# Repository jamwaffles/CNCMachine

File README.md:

# CNCMachine

LinuxCNC config and scripts for my DIY CNC machine

## NFS

<https://askubuntu.com/questions/7117/which-to-use-nfs-or-samba>

Better than Samba. `sudo apt install nfs-common`

In `/etc/fstab`:

```
192.168.0.9:/media/gangstacode  /home/james/GCode  nfs auto,_netdev,rw,hard,intr 0 0
```

## Mount samba share

```bash
mkdir ~/GCode
# yolo
chmod 0777 ~/GCode 
sudo apt install gvfs-backends samba cifs-utils
```

Then in `/etc/fstab`:

```
//octahedron.house/gangstacode /home/james/GCode cifs username=james,password=[password],iocharset=utf8,file_mode=0777,dir_mode=0777,noperm 0 0
```

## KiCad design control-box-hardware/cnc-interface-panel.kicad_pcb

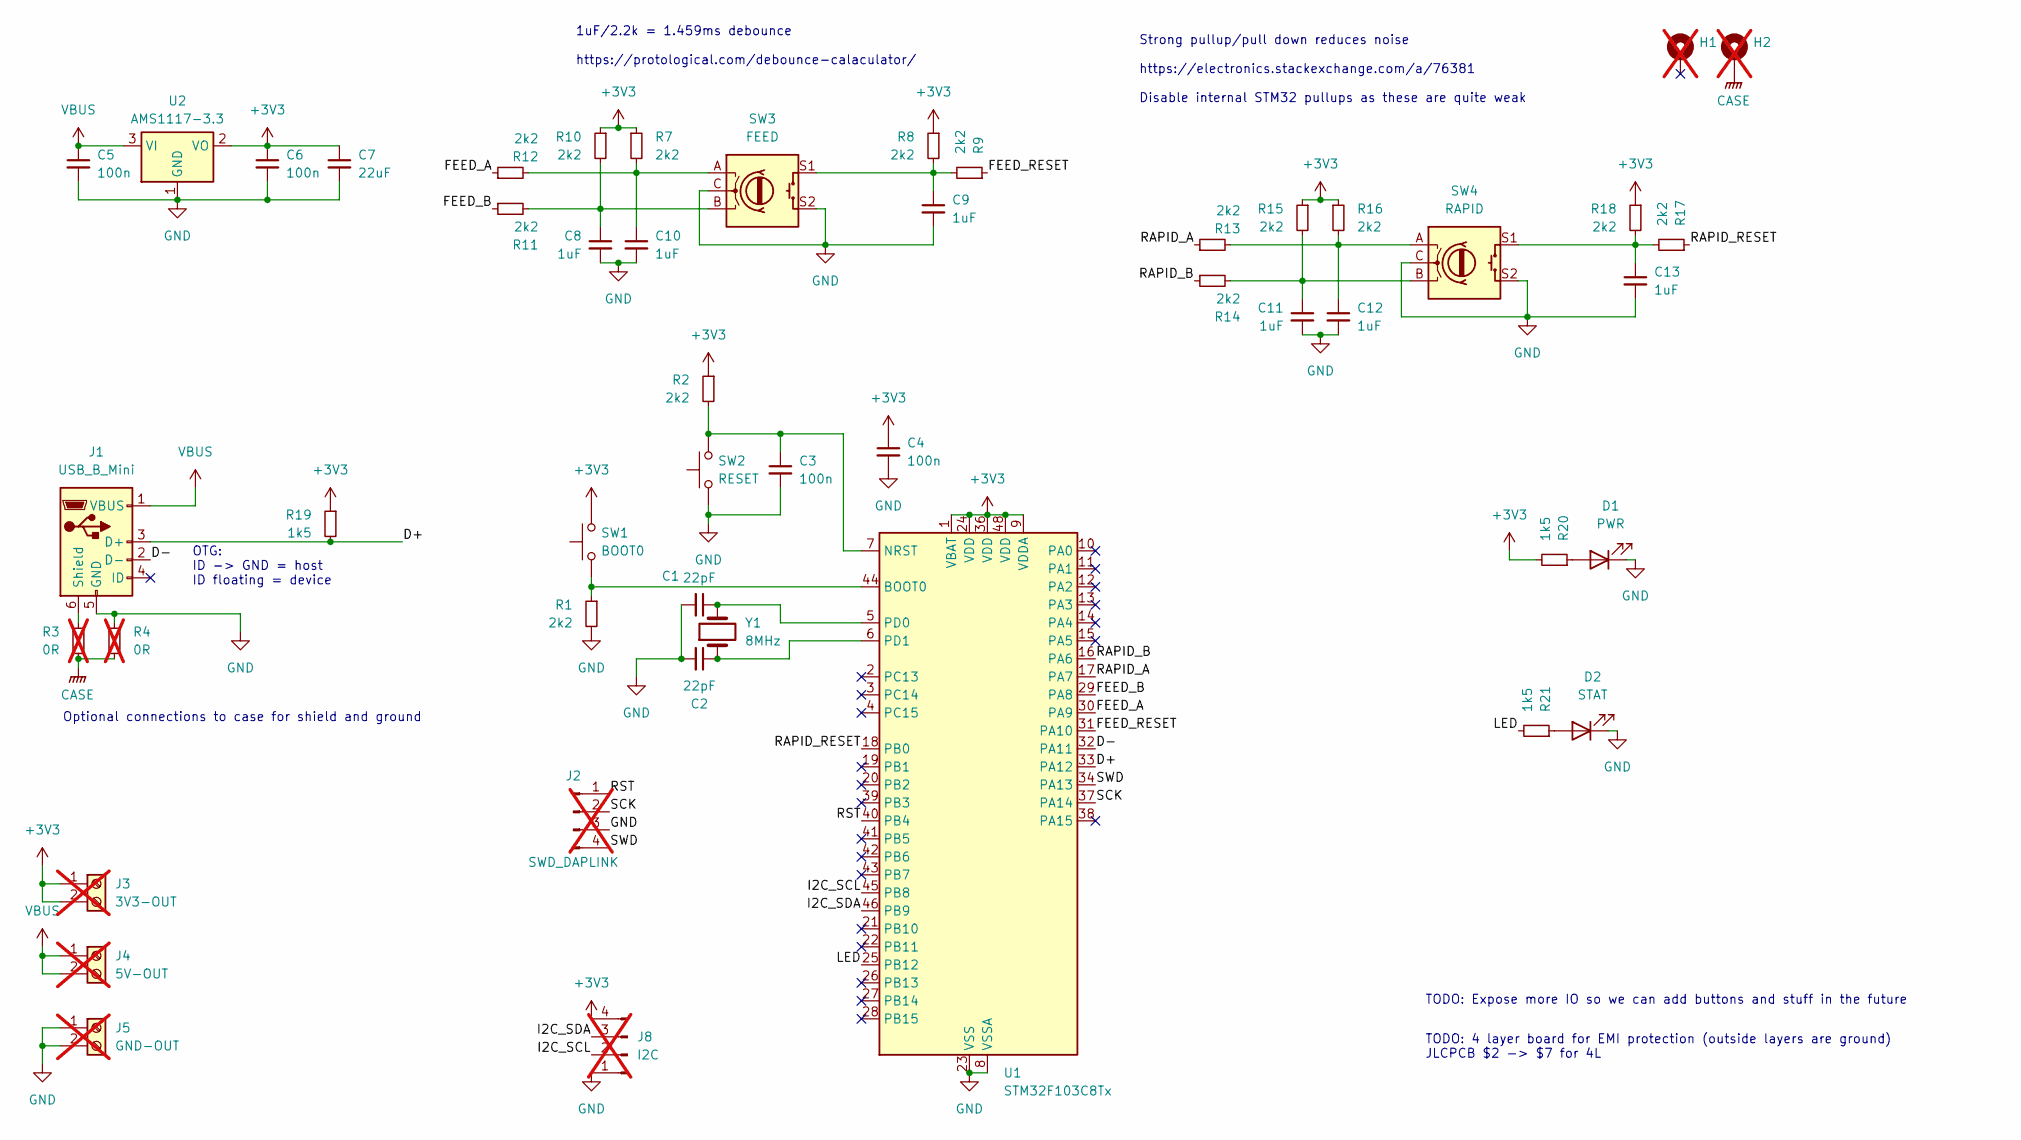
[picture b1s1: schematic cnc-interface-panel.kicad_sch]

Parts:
C1, C2: 22pF; C_0603_1608Metric_Pad1.08x0.95mm_HandSolder; MPN CL10C220JB8NNNC; JLCPCB C1653
C3, C4, C5, C6: 100n; C_0603_1608Metric_Pad1.08x0.95mm_HandSolder; MPN CC0603KRX7R9BB104; JLCPCB C14663
C7: 22uF; C_0603_1608Metric_Pad1.08x0.95mm_HandSolder; MPN CL10A226MQ8NRNC; JLCPCB C59461
C8, C9, C10, C11, C12, C13: 1uF; C_0603_1608Metric_Pad1.08x0.95mm_HandSolder; MPN CL10A105KB8NNNC; JLCPCB C15849
D1: PWR; LED_0603_1608Metric; MPN KT-0603W; JLCPCB C2290
D2: STAT; LED_0603_1608Metric; MPN KT-0603W; JLCPCB C2290
H1, H2: MountingHole_3.2mm_M3_Pad_Via; not fitted
J1: USB_B_Mini; molex-usb-mini-b-67503-1020; MPN 67503-1020; JLCPCB C136451
J2: SWD_DAPLINK; PinHeader_1x04_P2.54mm_Vertical; not fitted
J3: 3V3-OUT; TerminalBlock_Phoenix_MKDS-1,5-2_1x02_P5.00mm_Horizontal; not fitted
J4: 5V-OUT; TerminalBlock_Phoenix_MKDS-1,5-2_1x02_P5.00mm_Horizontal; not fitted
J5: GND-OUT; TerminalBlock_Phoenix_MKDS-1,5-2_1x02_P5.00mm_Horizontal; not fitted
J8: I2C; PinHeader_1x04_P2.54mm_Vertical; not fitted
R1, R2, R7, R8, R9, R10, R11, R12, R13, R14, R15, R16, R17, R18: 2k2; R_0603_1608Metric_Pad0.98x0.95mm_HandSolder; MPN 0603WAF2201T5E; JLCPCB C4190
R3, R4: 0R; R_0603_1608Metric_Pad0.98x0.95mm_HandSolder; MPN 0603WAF0000T5E; JLCPCB C21189; not fitted
R19, R20, R21: 1k5; R_0603_1608Metric_Pad0.98x0.95mm_HandSolder; MPN 0603WAF1501T5E; JLCPCB C22843
SW1: BOOT0; TS-1187A-B-A-B; MPN TS-1187A-B-A-B; JLCPCB C318884
SW2: RESET; TS-1187A-B-A-B; MPN TS-1187A-B-A-B; JLCPCB C318884
SW3: FEED; PEC11L4115FS0020; MPN PEC11L-4115F-S0020; JLCPCB C143799
SW4: RAPID; PEC11L4115FS0020; MPN PEC11L-4115F-S0020; JLCPCB C143799
U1: STM32F103C8Tx; LQFP-48_7x7mm_P0.5mm; MPN STM32F103C8T6; JLCPCB C8734
U2: AMS1117-3.3; SOT-223-3_TabPin2; MPN AMS1117-3.3; JLCPCB C6186
Y1: 8MHz; Crystal_SMD_TXC_7A-2Pin_5x3.2mm; MPN X50328MSB2GI; JLCPCB C115962

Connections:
+3V3: C4.1, C6.1, C7.1, J3.1, J3.2, J8.4, R2.1, R7.1, R8.1, R10.1, R15.1, R16.1, R18.1, R19.1, R20.2, SW1.2, U1.1 (VBAT), U1.9 (VDDA), U1.24 (VDD), U1.36 (VDD), U1.48 (VDD), U2.2 (VO)
/D+: J1.3 (D+), R19.2, U1.33 (PA12)
/D-: J1.2 (D-), U1.32 (PA11)
/FEED_A: R12.1, U1.30 (PA9)
/FEED_B: R11.1, U1.29 (PA8)
/FEED_RESET: R9.1, U1.31 (PA10)
/I2C_SCL: J8.2, U1.45 (PB8)
/I2C_SDA: J8.3, U1.46 (PB9)
/LED: R21.2, U1.25 (PB12)
/RAPID_A: R13.1, U1.17 (PA7)
/RAPID_B: R14.1, U1.16 (PA6)
/RAPID_RESET: R17.1, U1.18 (PB0)
/RST: J2.1, U1.40 (PB4)
/SCK: J2.2, U1.37 (PA14)
/SWD: J2.4, U1.34 (PA13)
CASE: H2.1, R3.2, R4.2
GND: C1.2, C2.2, C3.2, C4.2, C5.2, C6.2, C7.2, C8.2, C9.2, C10.2, C11.2, C12.2, C13.2, D1.1 (K), D2.1 (K), J1.5 (GND), J2.3, J5.1, J5.2, J8.1, R1.2, R4.1, SW2.1, SW3.C, SW3.S2, SW4.C, SW4.S2, U1.8 (VSSA), U1.23 (VSS), U1.35 (VSS), U1.47 (VSS), U2.1 (GND)
unnamed: C8.1, R10.2, R11.2, SW3.B
unnamed: C9.1, R8.2, R9.2, SW3.S1
unnamed: C10.1, R7.2, R12.2, SW3.A
unnamed: C11.1, R14.2, R15.2, SW4.B
unnamed: C12.1, R13.2, R16.2, SW4.A
unnamed: C13.1, R17.2, R18.2, SW4.S1
unnamed: D1.2 (A), R20.1
unnamed: D2.2 (A), R21.1
unnamed: J1.6 (Shield), R3.1
unnamed: R1.1, SW1.1, U1.44 (BOOT0)
unnamed: C3.1, R2.2, SW2.2, U1.7 (NRST)
unnamed: C1.1, U1.5 (PD0), Y1.2
unnamed: C2.1, U1.6 (PD1), Y1.1
VBUS: C5.1, J1.1 (VBUS), J4.1, J4.2, U2.3 (VI)

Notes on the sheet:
OTG: ID -> GND = host ID floating = device
Strong pullup/pull down reduces noise https://electronics.stackexchange.com/a/76381 Disable internal STM32 pullups as these are quite weak
Optional connections to case for shield and ground
TODO: 4 layer board for EMI protection (outside layers are ground) JLCPCB $2 -> $7 for 4L
1uF/2.2k = 1.459ms debounce https://protological.com/debounce-calaculator/
TODO: Expose more IO so we can add buttons and stuff in the future

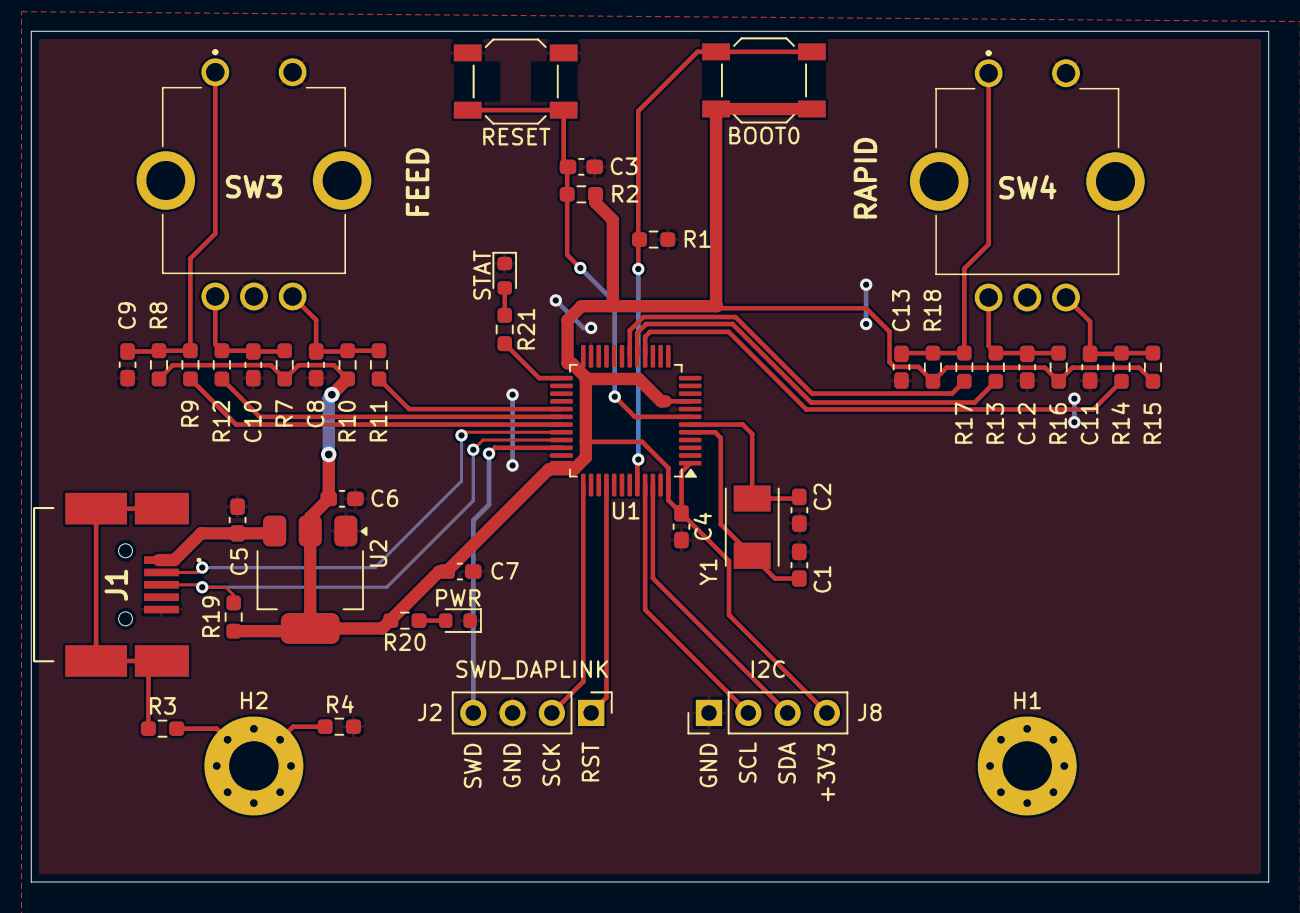
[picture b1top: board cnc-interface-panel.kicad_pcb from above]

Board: 2 copper layers, 80.0 x 55.0 mm, 46 parts (0 on the bottom side), 31 nets.

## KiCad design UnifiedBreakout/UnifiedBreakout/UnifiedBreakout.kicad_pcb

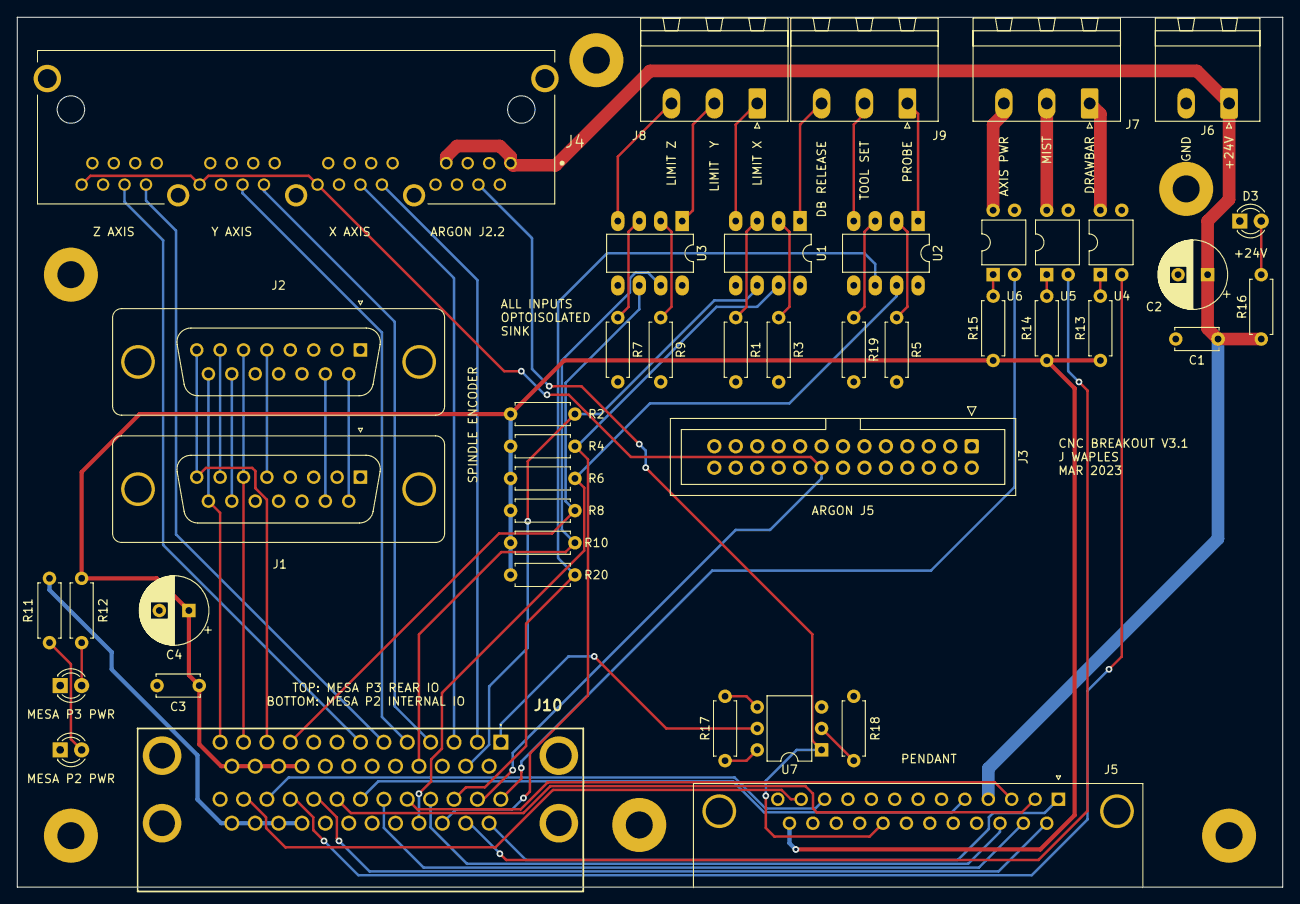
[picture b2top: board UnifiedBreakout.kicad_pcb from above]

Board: 2 copper layers, 149.9 x 103.0 mm, 50 parts (0 on the bottom side), 61 nets.

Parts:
C1, C3: 100n; C_Disc_D5.0mm_W2.5mm_P5.00mm
C2, C4: 100uF; CP_Radial_D8.0mm_P3.50mm
D1: MESA P3 PWR; LED_D3.0mm
D2: MESA P2 PWR; LED_D3.0mm
D3: +24V; LED_D3.0mm
H1, H2, H3, H4, H5, H6: MountingHole; MountingHole_3.2mm_M3_Pad
J1, J2: DA15_Receptacle_MountingHoles; DSUB-15_Female_Vertical_P2.77x2.84mm_MountingHoles
J3: ARGON J5; IDC-Header_2x13_P2.54mm_Vertical
J4: SS71800-041F
J5: PENDANT; DSUB-25_Female_Horizontal_P2.77x2.84mm_EdgePinOffset7.70mm_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
J6: 24V BUS; PhoenixContact_MSTBA_2,5_2-G-5,08_1x02_P5.08mm_Horizontal
J7: DRAWBAR+MIST+AXIS_PWR; PhoenixContact_MSTBA_2,5_3-G-5,08_1x03_P5.08mm_Horizontal
J8: LIMIT; PhoenixContact_MSTBA_2,5_3-G-5,08_1x03_P5.08mm_Horizontal
J9: AUX; PhoenixContact_MSTBA_2,5_3-G-5,08_1x03_P5.08mm_Horizontal
J10: DB25_Receptacle_Dual; NorComp-Dual-DB25
R1, R3, R5, R7, R9, R16, R18, R19: 2K2; R_Axial_DIN0207_L6.3mm_D2.5mm_P7.62mm_Horizontal
R2, R4, R6, R8, R10, R20: 10K; R_Axial_DIN0207_L6.3mm_D2.5mm_P7.62mm_Horizontal
R11, R12: 220R; R_Axial_DIN0207_L6.3mm_D2.5mm_P7.62mm_Horizontal
R13, R14, R15: 680R; R_Axial_DIN0207_L6.3mm_D2.5mm_P7.62mm_Horizontal
R17: 220K; R_Axial_DIN0207_L6.3mm_D2.5mm_P7.62mm_Horizontal
U1, U2, U3: ILD74; DIP-8_W7.62mm_LongPads
U4, U5, U6: G3VM-61A1; DIP-4_W7.62mm
U7: 4N35; DIP-6_W7.62mm

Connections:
+5VP: C3.1, C4.1, J5.25, J10.A22, J10.A23, J10.A24, J10.A25, R2.1, R4.1, R6.1, R8.1, R10.1, R11.2, R13.1, R14.1, R15.1, R20.1
+24V: C1.1, C2.1, J4.1_1, J4.7_1, J5.4, J6.1, R16.2
/ALARM: J3.16, J4.8_2, J4.8_3, J4.8_4, J10.B2
/ARGON ENCODER/A-: J1.7, J2.7
/ARGON ENCODER/B-: J1.5, J2.5
/ARGON ENCODER/IDX-: J1.14, J2.14
/ARGON ESTOP/ESTOP+: J4.4_1, J5.21, U7.1
/AXIS_PWR: J10.B1, U6.2
/DRAWBAR SW/INPUT: J9.3, U1.1
/DRAWBAR_SW: J10.B16, R4.2, U1.7
/DRAWBAR_VALVE: J10.B10, U4.2
/ESTOP: J10.A1, U7.5
/LIM X/INPUT: J8.1, U1.4
/LIM Y/INPUT: J8.2, U3.1
/LIM Z/INPUT: J8.3, U3.4
/LIMIT_X: J10.A15, R2.2, U1.6
/LIMIT_Y: J10.A17, R10.2, U3.7
/LIMIT_Z: J10.A10, R8.2, U3.6
/MESA P2 INTERNAL IO/MESA_5V: J10.B22, J10.B23, J10.B24, J10.B25, R12.1
/MESA P3 REAR IO/IO_02_STEPGEN_00_STEP: J4.2_2, J10.A2
/MESA P3 REAR IO/IO_04_STEPGEN_00_DIR: J4.4_2, J10.A3
/MESA P3 REAR IO/IO_06_STEPGEN_01_STEP: J4.2_3, J10.A4
/MESA P3 REAR IO/IO_08_STEPGEN_01_DIR: J4.4_3, J10.A5
/MESA P3 REAR IO/IO_09_STEPGEN_02_STEP: J4.2_4, J10.A6
/MESA P3 REAR IO/IO_10_STEPGEN_02_DIR: J4.4_4, J10.A7
/MESA_P3_5V: D2.2 (A), R12.2
/MIST: J10.B15, U5.2
/PENDANT_ENC_A: J5.11, J10.B11
/PENDANT_ENC_B: J5.12, J10.B12
/PENDANT_MULX1: J5.15, J10.B6
/PENDANT_MULX10: J5.3, J10.B5
/PENDANT_MULX100: J5.16, J10.B4
/PENDANT_SELA: J5.5, J10.B7
/PENDANT_SELX: J5.1, J10.B14
/PENDANT_SELY: J5.14, J10.B9
/PENDANT_SELZ: J5.2, J10.B8
/PROBE: J10.B17, R6.2, U2.7
/PROBE/INPUT: J9.1, U2.1
/SPINDLE_ENC_A: J1.8, J2.8, J10.A11
/SPINDLE_ENC_B: J1.6, J2.6, J10.A12
/SPINDLE_ENC_IDX: J1.15, J2.15, J10.A13
/TOOL_PROBE: J10.B3, R20.2, U2.6
/TOOL_PROBE/INPUT: J9.2, U2.4
GND: C1.2, C2.2, C3.2, C4.2, D1.1 (K), D2.1 (K), D3.1 (K), J1.0 (PAD), J1.10, J2.0 (PAD), J2.10, J3.1, J3.15, J4.1_2, J4.1_3, J4.1_4, J4.3_2, J4.3_3, J4.3_4, J4.5_1, J4.5_2, J4.5_3, J4.5_4, J4.7_2, J4.7_3, J4.7_4, J4.8_1, J5.0 (PAD), J5.19, J5.20, J6.2, J10.A18, J10.A19, J10.A20, J10.A21, J10.B18, J10.B19, J10.B20, J10.B21, J10.MH1, J10.MH2, J10.MH3, J10.MH4, R1.2, R3.2, R5.2, R7.2, R9.2, R17.2, R18.2, R19.2, U1.5, U1.8, U2.5, U2.8, U3.5, U3.8, U4.3, U5.3, U6.3, U7.4
unnamed: D1.2 (A), R11.1
unnamed: D3.2 (A), R16.1
unnamed: J1.9, J2.9
unnamed: J7.1, U4.4
unnamed: J7.2, U5.4
unnamed: J7.3, U6.4
unnamed: R1.1, U1.3
unnamed: R3.1, U1.2
unnamed: R5.1, U2.2
unnamed: R7.1, U3.3
unnamed: R9.1, U3.2
unnamed: R13.2, U4.1
unnamed: R14.2, U5.1
unnamed: R15.2, U6.1
unnamed: R17.1, U7.6
unnamed: R18.1, U7.2
unnamed: R19.1, U2.3

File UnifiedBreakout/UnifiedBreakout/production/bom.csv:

Designator,Footprint,Quantity,Value,LCSC Part #
"C1, C3",C_Disc_D5.0mm_W2.5mm_P5.00mm,2,100n,K104K15X7RF53H5
"C2, C4",CP_Radial_D8.0mm_P3.50mm,2,100uF,35RX30100M8X11.5 
D1,LED_D3.0mm,1,MESA P3 PWR,MCL034GD 
D2,LED_D3.0mm,1,MESA P2 PWR,MCL034GD 
D3,LED_D3.0mm,1,+24V,MCL034MT
"H1, H2, H3, H4, H5, H6",MountingHole_3.2mm_M3_Pad,6,MountingHole,
"J1, J2",DSUB-15_Female_Vertical_P2.77x2.84mm_MountingHoles,2,DA15_Receptacle_MountingHoles,D15S24A4GV00LF 
J10,NorComp-Dual-DB25,1,DB25_Receptacle_Dual,178-025-513R571
J3,IDC-Header_2x13_P2.54mm_Vertical,1,ARGON J5,61202621621
J4,SS71800-041F,1,~,SS71800-041F
J5,DSUB-25_Female_Horizontal_P2.77x2.84mm_EdgePinOffset7.70mm_Housed_MountingHolesOffset9.12mm,1,PENDANT,5747846-4 
J6,"PhoenixContact_MSTBA_2,5_2-G-5,08_1x02_P5.08mm_Horizontal",1,24V BUS,1757242
J7,"PhoenixContact_MSTBA_2,5_3-G-5,08_1x03_P5.08mm_Horizontal",1,DRAWBAR+MIST+AXIS_PWR,1757255
J8,"PhoenixContact_MSTBA_2,5_3-G-5,08_1x03_P5.08mm_Horizontal",1,LIMIT,1757255
J9,"PhoenixContact_MSTBA_2,5_3-G-5,08_1x03_P5.08mm_Horizontal",1,AUX,1757255
"R1, R16, R18, R19, R3, R5, R7, R9",R_Axial_DIN0207_L6.3mm_D2.5mm_P7.62mm_Horizontal,8,2K2,MF25 2K2
"R10, R2, R20, R4, R6, R8",R_Axial_DIN0207_L6.3mm_D2.5mm_P7.62mm_Horizontal,6,10K,MF25 10K
"R11, R12",R_Axial_DIN0207_L6.3mm_D2.5mm_P7.62mm_Horizontal,2,220R,MF25 220R
"R13, R14, R15",R_Axial_DIN0207_L6.3mm_D2.5mm_P7.62mm_Horizontal,3,680R,MF25 680R
R17,R_Axial_DIN0207_L6.3mm_D2.5mm_P7.62mm_Horizontal,1,220K,MF25 220K
"U1, U2, U3",DIP-8_W7.62mm_LongPads,3,ILD74,ILD74 
"U4, U5, U6",DIP-4_W7.62mm,3,G3VM-61A1 ,G3VM-61A1
U7,DIP-6_W7.62mm,1,4N35,4N35

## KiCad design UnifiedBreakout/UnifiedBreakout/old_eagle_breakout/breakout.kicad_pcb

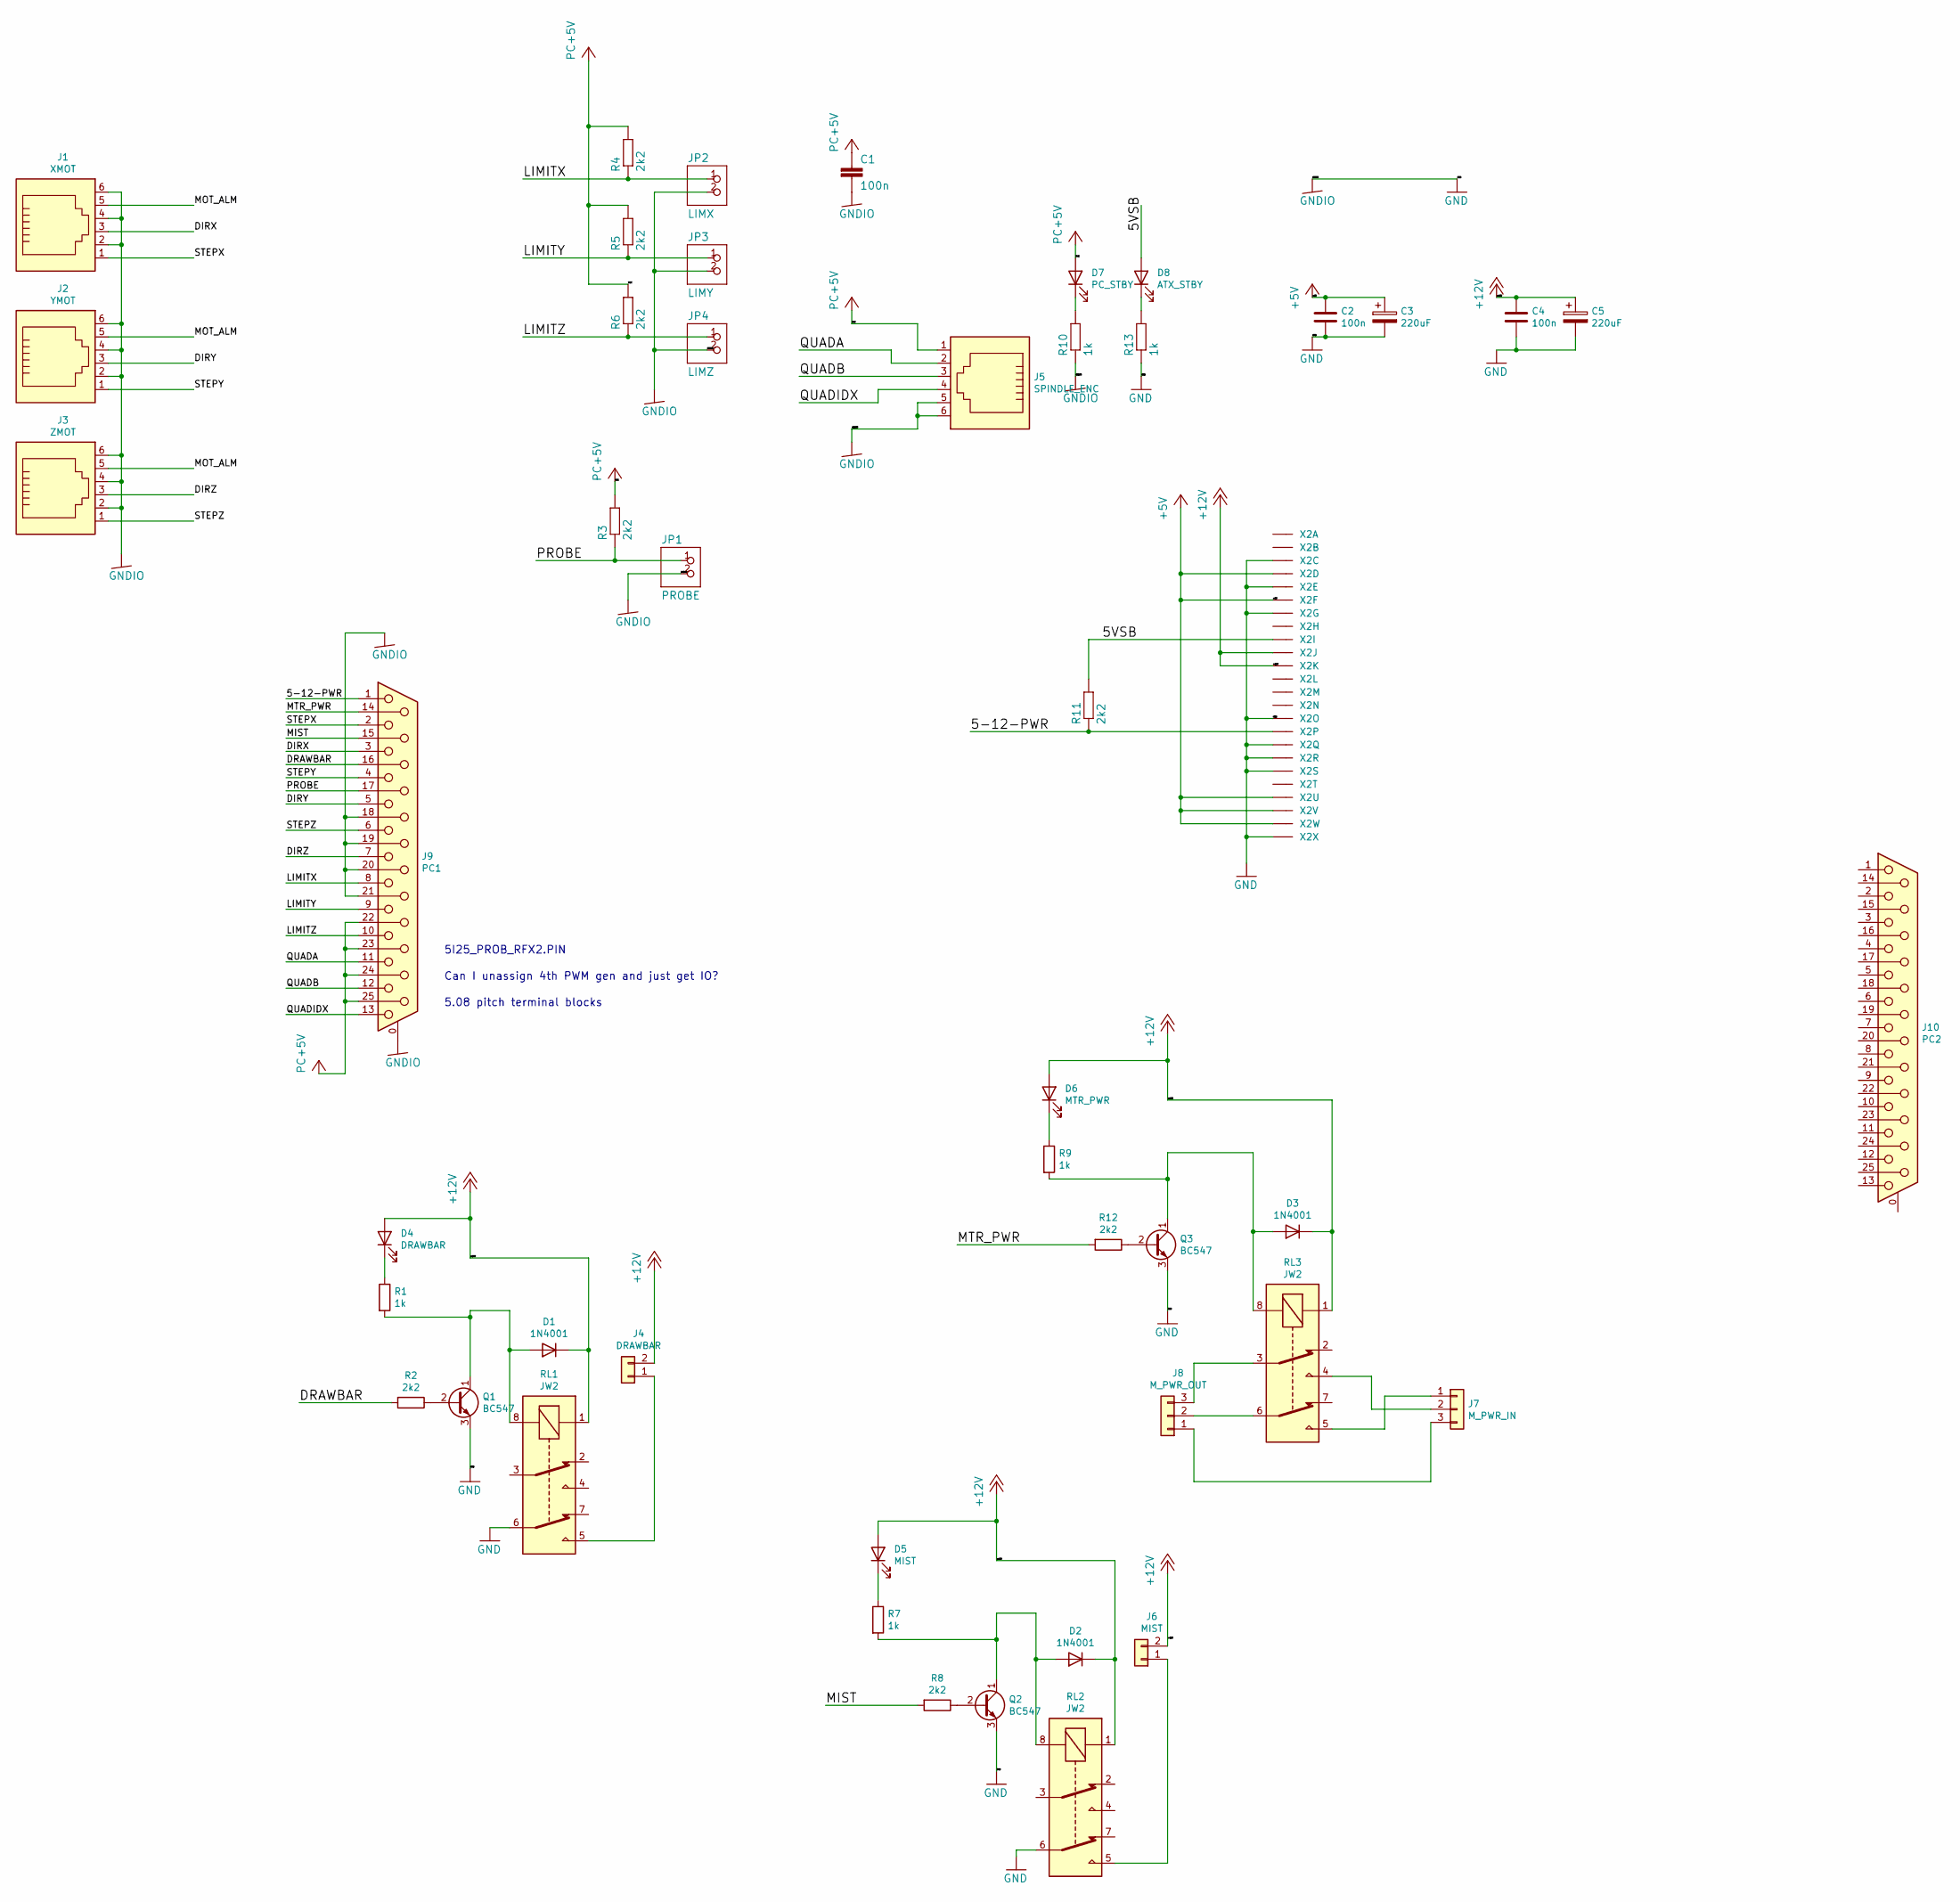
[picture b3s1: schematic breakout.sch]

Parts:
C1: 100n; C_Rect_L7.0mm_W2.5mm_P5.00mm
C2, C4: 100n; C_Disc_D8.0mm_W2.5mm_P5.00mm
C3, C5: 220uF; CP_Radial_D8.0mm_P3.80mm
D1, D2, D3: 1N4001; D_DO-41_SOD81_P10.16mm_Horizontal
D4: DRAWBAR; LED_D3.0mm
D5: MIST; LED_D3.0mm
D6: MTR_PWR; LED_D3.0mm
D7: PC_STBY; LED_D3.0mm
D8: ATX_STBY; LED_D3.0mm
J1: XMOT; 6p6c
J2: YMOT; 6p6c
J3: ZMOT; 6p6c
J4: DRAWBAR; kk156_26-60-4020
J5: SPINDLE_ENC; 6p6c
J6: MIST; kk156_26-60-4020
J7: M_PWR_IN; kk156_26-60-4030
J8: M_PWR_OUT; kk156_26-60-4030
J9: PC1; DB_25F
J10: PC2; DB_25F
JP1: PROBE; rca_yellow
JP2: LIMX; rca_black
JP3: LIMY; rca_black
JP4: LIMZ; rca_black
Q1, Q2, Q3: BC547; TO-92_Inline_Wide
R1, R7, R9, R10, R13: 1k; R_Axial_DIN0207_L6.3mm_D2.5mm_P7.62mm_Horizontal
R2, R3, R4, R5, R6, R8, R11, R12: 2k2; R_Axial_DIN0207_L6.3mm_D2.5mm_P7.62mm_Horizontal
RL1, RL2, RL3: JW2; Relay_DPDT_Panasonic_JW2
X2: 5566-24; Molex_Mini-Fit_Jr_5566-24A_2x12_P4.20mm_Vertical

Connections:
+5V: C2.1, C3.1, X2.4, X2.6, X2.21, X2.22, X2.23
+12V: C4.1, C5.1, D1.1 (K), D2.1 (K), D3.1 (K), D4.2 (A), D5.2 (A), D6.2 (A), J4.2, J6.2, RL1.1, RL2.1, RL3.1, X2.10, X2.11
/5-12-PWR: J9.1, R11.1, X2.16; also elsewhere on the board
/5VSB: D8.2 (A), R11.2, X2.9
/DIRX: J1.3, J9.3; also elsewhere on the board
/DIRY: J2.3, J9.5; also elsewhere on the board
/DIRZ: J3.3, J9.7; also elsewhere on the board
/DRAWBAR: J9.16, R2.2; also elsewhere on the board
/LIMITX: J9.8, JP2.1, R4.1; also elsewhere on the board
/LIMITY: J9.9, JP3.1, R5.1; also elsewhere on the board
/LIMITZ: J9.10, JP4.1, R6.1; also elsewhere on the board
/MIST: J9.15, R8.2; also elsewhere on the board
/MOT_ALM: J1.5, J2.5, J3.5
/MTR_PWR: J9.14, R12.2; also elsewhere on the board
/PROBE: J9.17, JP1.1, R3.1; also elsewhere on the board
/QUADA: J5.2, J9.11; also elsewhere on the board
/QUADB: J5.3, J9.12; also elsewhere on the board
/QUADIDX: J5.4, J9.13; also elsewhere on the board
/STEPX: J1.1, J9.2; also elsewhere on the board
/STEPY: J2.1, J9.4; also elsewhere on the board
/STEPZ: J3.1, J9.6; also elsewhere on the board
GND: C1.2, C2.2, C3.2, C4.2, C5.2, J1.2, J1.4, J1.6, J2.2, J2.4, J2.6, J3.2, J3.4, J3.6, J5.5, J5.6, J9.0 (PAD), J9.18, J9.19, J9.20, J9.21, JP1.2, JP2.2, JP3.2, JP4.2, Q1.3 (E), Q2.3 (E), Q3.3 (E), R10.1, R13.1, RL1.6, RL2.6, X2.3, X2.5, X2.7, X2.15, X2.17, X2.18, X2.19, X2.24; also elsewhere on the board
unnamed: D1.2 (A), Q1.1 (C), R1.2, RL1.8
unnamed: D2.2 (A), Q2.1 (C), R7.2, RL2.8
unnamed: D3.2 (A), Q3.1 (C), R9.2, RL3.8
unnamed: D4.1 (K), R1.1
unnamed: D5.1 (K), R7.1
unnamed: D6.1 (K), R9.1
unnamed: D7.1 (K), R10.2
unnamed: D8.1 (K), R13.2
unnamed: J4.1, RL1.5
unnamed: J6.1, RL2.5
unnamed: J7.1, RL3.5
unnamed: J7.2, RL3.4
unnamed: J7.3, J8.1
unnamed: J8.2, RL3.6
unnamed: J8.3, RL3.3
unnamed: Q1.2 (B), R2.1
unnamed: Q2.2 (B), R8.1
unnamed: Q3.2 (B), R12.1
VCC: C1.1, D7.2 (A), J5.1, J9.22, J9.23, J9.24, J9.25, R3.2, R4.2, R5.2, R6.2; also elsewhere on the board

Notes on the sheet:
5I25_PROB_RFX2.PIN
5.08 pitch terminal blocks
Can I unassign 4th PWM gen and just get IO?

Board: 2 copper layers, 48 parts (0 on the bottom side), 41 nets, no tracks yet.

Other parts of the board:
X1: PC; DB_25F

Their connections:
/5-12-PWR: X1.1; also elsewhere on the board
/DIRX: X1.3; also elsewhere on the board
/DIRY: X1.5; also elsewhere on the board
/DIRZ: X1.7; also elsewhere on the board
/DRAWBAR: X1.16; also elsewhere on the board
/LIMITX: X1.8; also elsewhere on the board
/LIMITY: X1.9; also elsewhere on the board
/LIMITZ: X1.10; also elsewhere on the board
/MIST: X1.15; also elsewhere on the board
/MTR_PWR: X1.14; also elsewhere on the board
/PROBE: X1.17; also elsewhere on the board
/QUADA: X1.11; also elsewhere on the board
/QUADB: X1.12; also elsewhere on the board
/QUADIDX: X1.13; also elsewhere on the board
/STEPX: X1.2; also elsewhere on the board
/STEPY: X1.4; also elsewhere on the board
/STEPZ: X1.6; also elsewhere on the board
GND: X1.18, X1.19, X1.20, X1.21; also elsewhere on the board
VCC: X1.22, X1.23, X1.24, X1.25; also elsewhere on the board

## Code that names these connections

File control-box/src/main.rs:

#![no_std]
#![no_main]

use control_box_common::Outputs;
use core::sync::atomic::{AtomicBool, Ordering};
use defmt_rtt as _;
use embassy_executor::Spawner;
use embassy_futures::join::join;
use embassy_stm32::{
    bind_interrupts,
    exti::ExtiInput,
    gpio::{Input, Level, Output, Pull, Speed},
    peripherals::{self, PA10, PB0},
    time::Hertz,
    timer::qei::{Direction, Qei, QeiPin},
    usb::{self, Driver},
    Config,
};
use embassy_time::{Duration, Ticker, Timer};
use embassy_usb::{
    class::cdc_acm::{CdcAcmClass, State},
    driver::EndpointError,
    Builder,
};
use embedded_hal::digital::OutputPin;
use panic_probe as _;

const VID: u16 = 0xaabb;
const PID: u16 = 0xccdd;

static ENCODER_BUTTON1: AtomicBool = AtomicBool::new(false);
static ENCODER_BUTTON2: AtomicBool = AtomicBool::new(false);

bind_interrupts!(struct Irqs {
    USB_LP_CAN1_RX0 => usb::InterruptHandler<peripherals::USB>;
});

#[embassy_executor::task]
async fn heartbeat_task(mut led: impl OutputPin + 'static) -> ! {
    loop {
        let _ = led.set_low();
        Timer::after(Duration::from_millis(200)).await;

        let _ = led.set_high();
        Timer::after(Duration::from_millis(800)).await;
    }
}

#[embassy_executor::task]
async fn button1_task(mut button1: ExtiInput<'static, PA10>) -> ! {
    loop {
        button1.wait_for_any_edge().await;

        // Active low
        let state = !button1.is_high();

        defmt::info!("B1 changed to {}", state);

        ENCODER_BUTTON1.store(state, Ordering::Relaxed);
    }
}

#[embassy_executor::task]
async fn button2_task(mut button2: ExtiInput<'static, PB0>) -> ! {
    loop {
        button2.wait_for_any_edge().await;

        // Active low
        let state = !button2.is_high();

        defmt::info!("B2 changed to {}", state);

        ENCODER_BUTTON2.store(state, Ordering::Relaxed);
    }
}

#[embassy_executor::main]
async fn main(spawner: Spawner) {
    let mut config = Config::default();
    config.rcc.hse = Some(Hertz(8_000_000));
    config.rcc.sys_ck = Some(Hertz(48_000_000));
    config.rcc.pclk1 = Some(Hertz(24_000_000));
    let mut p = embassy_stm32::init(config);

    defmt::info!("Starting up");

    {
        // BluePill board has a pull-up resistor on the D+ line.
        // Pull the D+ pin down to send a RESET condition to the USB bus.
        // This forced reset is needed only for development, without it host
        // will not reset your device when you upload new firmware.
        let _dp = Output::new(&mut p.PA12, Level::Low, Speed::Low);
        Timer::after_millis(10).await;
    }

    // Create the driver, from the HAL.
    let driver = Driver::new(p.USB, Irqs, p.PA12, p.PA11);

    // Create embassy-usb Config
    let config = embassy_usb::Config::new(VID, PID);

    // Create embassy-usb DeviceBuilder using the driver and config.
    // It needs some buffers for building the descriptors.
    let mut device_descriptor = [0; 256];
    let mut config_descriptor = [0; 256];
    let mut bos_descriptor = [0; 256];
    let mut control_buf = [0; 7];

    let mut state = State::new();

    let mut builder = Builder::new(
        driver,
        config,
        &mut device_descriptor,
        &mut config_descriptor,
        &mut bos_descriptor,
        &mut [], // no msos descriptors
        &mut control_buf,
    );

    // Create classes on the builder.
    let mut class = CdcAcmClass::new(&mut builder, &mut state, 64);

    // Build the builder.
    let mut usb = builder.build();

    // Run the USB device.
    let usb_fut = usb.run();

    // // Do stuff with the class!
    // let echo_fut = async {
    //     loop {
    //         class.wait_connection().await;
    //         defmt::info!("Connected");
    //         let _ = echo(&mut class).await;
    //         defmt::info!("Disconnected");
    //     }
    // };

    // Black pill/blue pill user LED on PC13, active low
    // let led = Output::new(p.PC13, Level::Low, Speed::Low);
    // Or for the black version of the blue pill with mounting holes
    let mut led = Output::new(p.PB12, Level::High, Speed::Low);

    let encoder1 = Qei::new(p.TIM1, QeiPin::new_ch1(p.PA8), QeiPin::new_ch2(p.PA9));
    let encoder2 = Qei::new(p.TIM3, QeiPin::new_ch1(p.PA6), QeiPin::new_ch2(p.PA7));

    let button1 = Input::new(p.PA10, Pull::Down);
    let button1 = ExtiInput::new(button1, p.EXTI10);
    let button2 = Input::new(p.PB0, Pull::Down);
    let button2 = ExtiInput::new(button2, p.EXTI0);

    // defmt::unwrap!(spawner.spawn(heartbeat_task(led)));
    defmt::unwrap!(spawner.spawn(button1_task(button1)));
    defmt::unwrap!(spawner.spawn(button2_task(button2)));
    // defmt::unwrap!(spawner.spawn(heartbeat_task(led)));

    defmt::info!("Begin loop");

    let mut ticker = Ticker::every(Duration::from_millis(5));

    let mut prev = Outputs::default();

    let encoder_task = async {
        let mut out_buf = [0u8; 256];

        loop {
            defmt::info!("Waiting for connection");

            class.wait_connection().await;

            defmt::info!("USB is connected");

            // let dir1 = match encoder1.read_direction() {
            //     Direction::Upcounting => "↑",
            //     Direction::Downcounting => "↓",
            // };
            // let dir2 = match encoder2.read_direction() {
            //     Direction::Upcounting => "↑",
            //     Direction::Downcounting => "↓",
            // };

            // Divide by 4 because quadrature
            // defmt::info!(
            //     "{} {} | {} {}",
            //     encoder1.count() / 4,
            //     dir1,
            //     encoder2.count() / 4,
            //     dir2
            // );

            // ENCODER1.store(encoder1.count(), Ordering::Relaxed);
            // ENCODER2.store(encoder2.count(), Ordering::Relaxed);

            loop {
                let data = Outputs {
                    encoder1: encoder1.count(),
                    encoder2: encoder2.count(),
                    encoder1_up: matches!(encoder1.read_direction(), Direction::Upcounting),
                    encoder2_up: matches!(encoder2.read_direction(), Direction::Upcounting),
                    encoder_button1: ENCODER_BUTTON1.load(Ordering::Relaxed),
                    encoder_button2: ENCODER_BUTTON2.load(Ordering::Relaxed),
                };

                if data != prev {
                    if let Ok(send) = data.encode(&mut out_buf) {
                        if let Err(EndpointError::Disabled) = class.write_packet(send).await {
                            defmt::info!("USB is disconnected");

                            // Turn off
                            led.set_high();

                            break;
                        } else {
                            led.toggle();
                        }
                    }

                    prev = data;
                }

                ticker.next().await;
            }
        }
    };

    join(encoder_task, usb_fut).await;
}

// struct Disconnected {}

// impl From<EndpointError> for Disconnected {
//     fn from(val: EndpointError) -> Self {
//         match val {
//             EndpointError::BufferOverflow => panic!("Buffer overflow"),
//             EndpointError::Disabled => Disconnected {},
//         }
//     }
// }

// async fn echo<'d, T: Instance + 'd>(
//     class: &mut CdcAcmClass<'d, Driver<'d, T>>,
// ) -> Result<(), Disconnected> {
//     let mut buf = [0; 64];
//     let mut out_buf = [0u8; 128];

//     loop {
//         let n = class.read_packet(&mut buf).await?;

//         let data = &buf[..n];

//         defmt::info!("data: {:x}", data);

//         let count = cobs::encode_with_sentinel(data, &mut out_buf, b'\n');

//         let ret = &out_buf[0..count];

//         class.write_packet(ret).await?;
//     }
// }
